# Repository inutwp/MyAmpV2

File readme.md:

Desktop Hybrid/Opamp Amp.

- 3CH Schema with DualOpamp Gain and DualOpamp / Discrete Buffer
- Discrete RailSpliter with Capacitance Multiplier

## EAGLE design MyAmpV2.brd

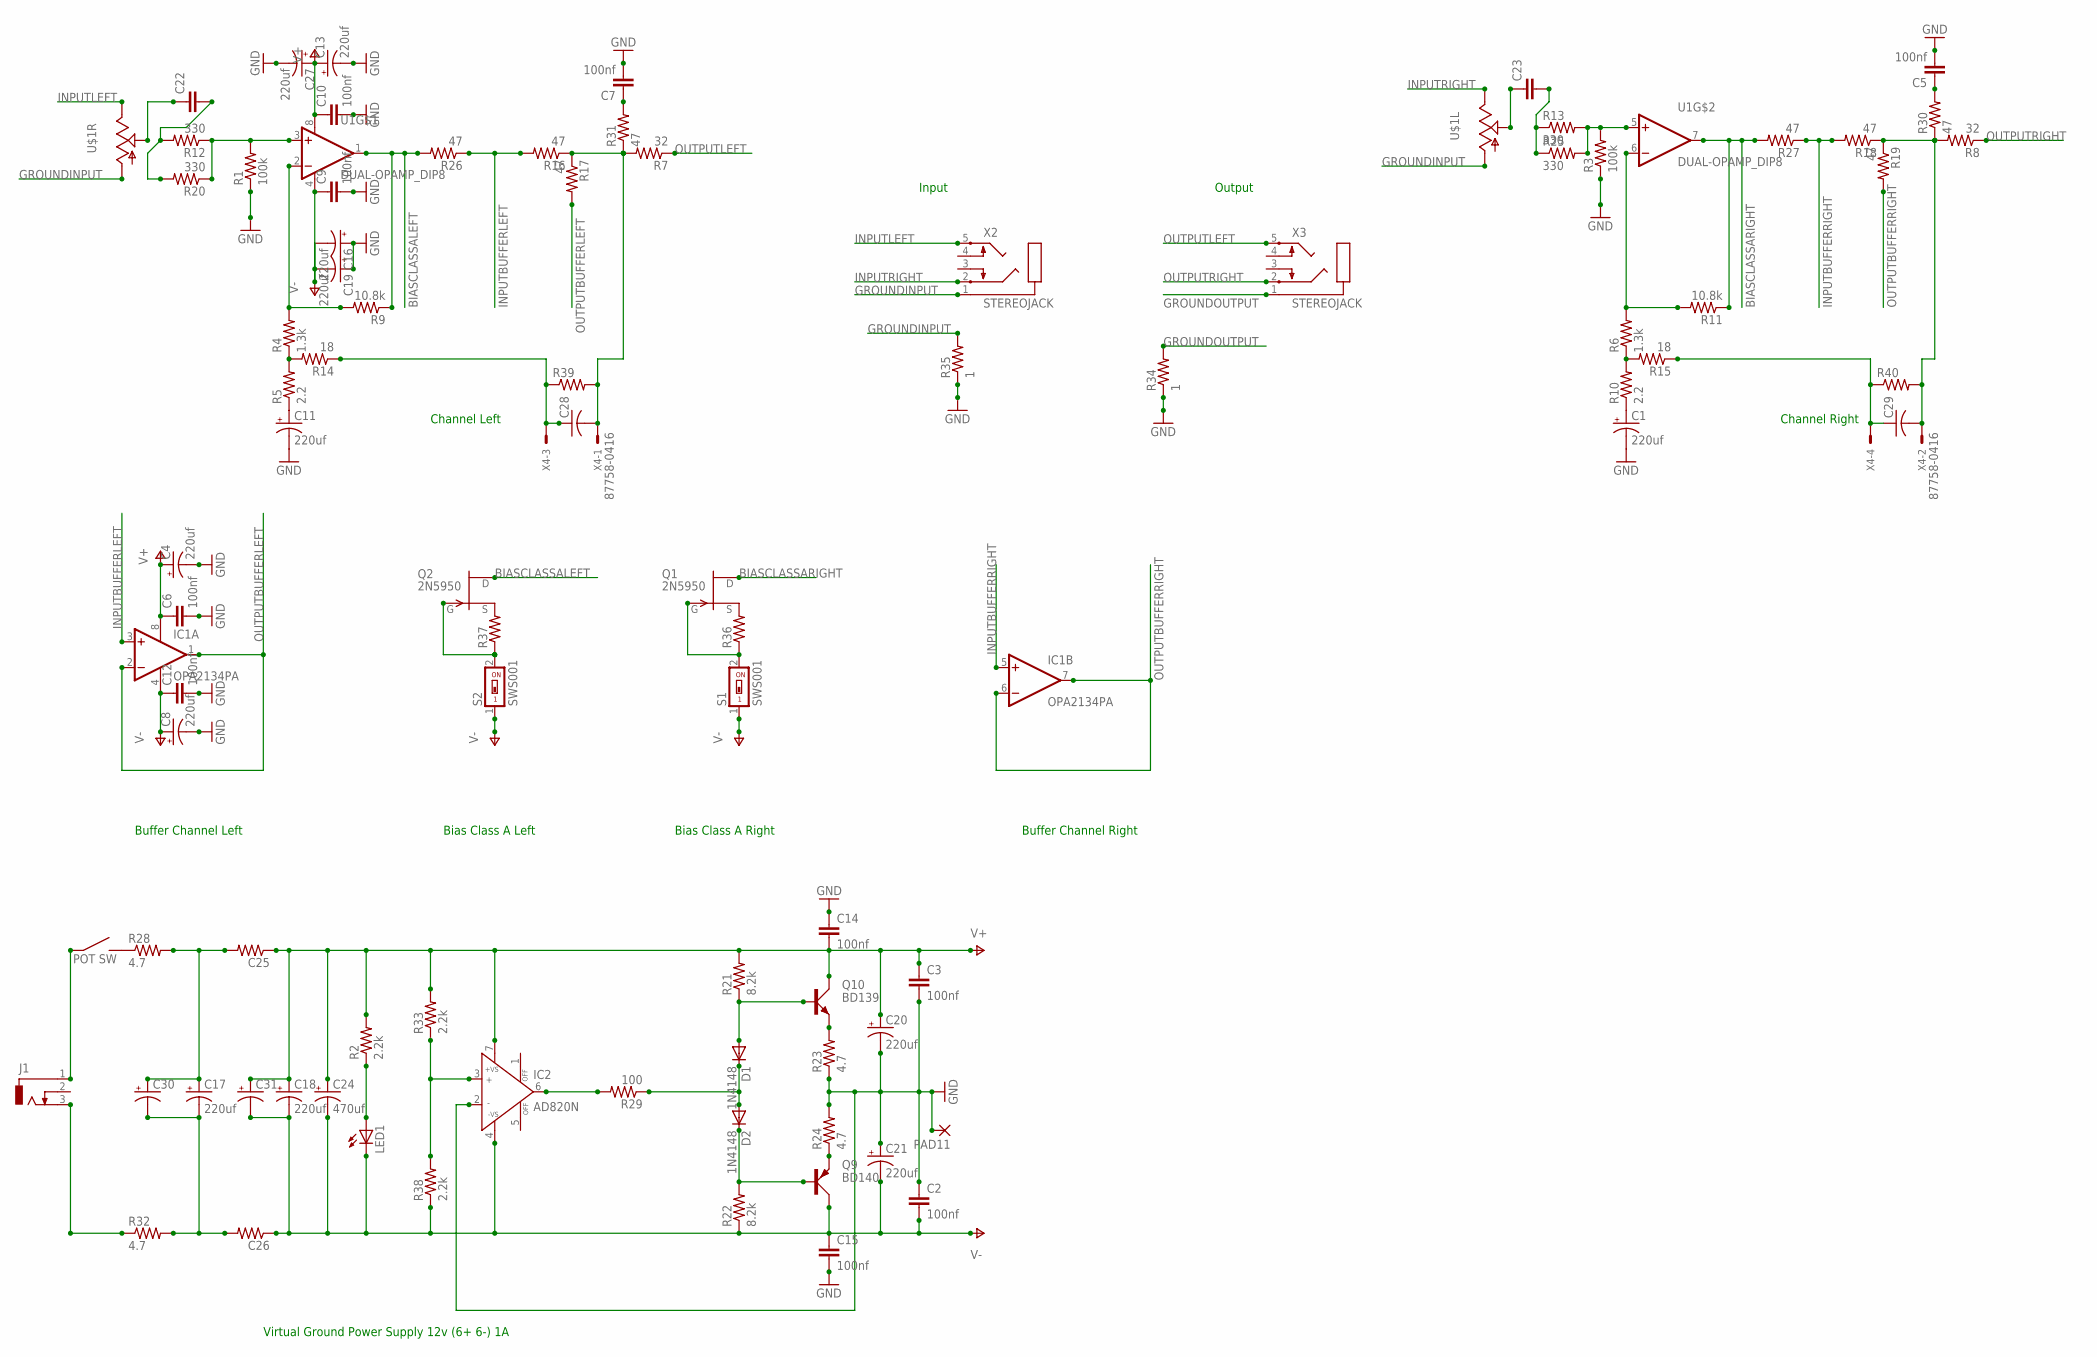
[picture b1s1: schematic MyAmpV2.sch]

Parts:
C1, C4, C8, C11, C13, C16, C17, C18, C19, C27: 220uf; E5-10,5
C2, C3, C5, C6, C7, C9, C10, C12, C14, C15: 100nf; C5B2.5
C20, C21: 220uf; D/7343-31R
C22, C23: C22/6; C22.5B6
C24: 470uf; E5-10,5
C25, C26: R-US_0207/12; 0207/12
C28, C29: C-USC1206K; C1206K
C30, C31: CPOL-USE7.5-16; E7,5-16
D1, D2: 1N4148; DO35-7
IC1: OPA2134PA; DIL08
IC2: AD820N; DIL08
J1: DCJ0303
LED1: LED3MM
PAD11: 1,6/0,9
Q1, Q2: 2N5950; TO-92
Q9: BD140; TO126AV
Q10: BD139; TO126AV
R1, R3: 100k; 0207/10
R2, R33, R38: 2.2k; 0207/10
R4, R6: 1.3k; 0207/10
R5, R10: 2.2; 0204/5
R7, R8: 32; 0207/12
R9, R11: 10.8k; 0207/10
R12, R13, R20, R25: 330; 0207/10
R14, R15: 18; 0207/12
R16, R17, R18, R19: 47; 0207/12
R21, R22: 8.2k; 0207/10
R23, R24, R28, R32: 4.7; 0207/10
R26, R27: 47; 0207/10
R29: 100; 0207/10
R30, R31: 47; 0207/7
R34, R35: 1; 0207/7
R36, R37: R-US_0204/5; 0204/5
R39, R40: R-US_MELF0204W; MINI_MELF-0204W
S1, S2: SWS001; SMS-001
U1: DUAL-OPAMP_DIP8; DIP-8
U$1: ALPS_RK0971221Z05; ALPS_RK0971221Z0X
X2, X3: STEREOJACK; STX3100
X4: 87758-0416

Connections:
BIASCLASSALEFT: Q2.3 (D), R9.1, R26.2, U1.1 (OUT)
BIASCLASSARIGHT: Q1.3 (D), R11.1, R27.2, U1.7 (OUT)
GND: C1.-, C2.1, C3.2, C4.-, C5.2, C6.2, C7.2, C8.-, C9.2, C10.2, C11.-, C12.2, C13.-, C14.1, C15.2, C16.+, C19.+, C20.-, C21.+, C27.-, IC2.2 (IN-), PAD11.1, R1.1, R3.1, R23.1, R24.2, R34.1, R35.1
GROUNDINPUT: R35.2, U$1.G1 (1), U$1.G2 (1), X2.1
GROUNDOUTPUT: R34.2, X3.1
INPUTBUFFERLEFT: IC1.3 (+IN), R16.2, R26.1
INPUTBUFFERRIGHT: IC1.5 (+IN), R18.2, R27.1
INPUTLEFT: U$1.I2 (3), X2.5
INPUTRIGHT: U$1.I1 (3), X2.2
unnamed: R1.2, R12.1, R20.1, U1.3 (+IN)
unnamed: C1.+, R10.1
unnamed: C22.2, R12.2, R20.2
unnamed: C11.+, R5.1
unnamed: IC2.6 (OUT), R29.2
unnamed: Q10.E, R23.2
unnamed: IC2.3 (IN+), R33.1, R38.2
unnamed: Q9.E, R24.1
unnamed: C22.1, U$1.O2 (2)
unnamed: R3.2, R13.2, R25.2, U1.5 (+IN)
unnamed: C23.2, R13.1, R25.1
unnamed: R4.1, R5.2, R14.2
unnamed: R4.2, R9.2, U1.2 (-IN)
unnamed: R6.1, R10.2, R15.2
unnamed: C23.1, U$1.O1 (2)
unnamed: C29.1, R15.1, R40.1, X4.4
unnamed: C28.2, R7.2, R16.1, R17.1, R31.1, R39.2, X4.1
unnamed: R6.2, R11.2, U1.6 (-IN)
unnamed: C28.1, R14.1, R39.1, X4.3
unnamed: R28.1, U$1.S2
unnamed: J1.3, R32.1
unnamed: C29.2, R8.2, R18.1, R19.1, R30.1, R40.2, X4.2
unnamed: LED1.A, R2.1
unnamed: J1.1, U$1.S1
unnamed: C5.1, R30.2
unnamed: D1.A, Q10.B, R21.1
unnamed: D2.C, Q9.B, R22.2
unnamed: C17.+, C25.2, C30.+, R28.2
unnamed: D1.C, D2.A, R29.1
unnamed: C7.1, R31.2
unnamed: C17.-, C26.2, C30.-, R32.2
unnamed: Q1.2 (S), R36.2
unnamed: Q2.1 (G), R37.1, S2.2
unnamed: Q1.1 (G), R36.1, S1.2
unnamed: Q2.2 (S), R37.2
OUTPUTBUFFERLEFT: IC1.1 (OUT), IC1.2 (-IN), R17.2
OUTPUTBUFFERRIGHT: IC1.6 (-IN), IC1.7 (OUT), R19.2
OUTPUTLEFT: R7.1, X3.5
OUTPUTRIGHT: R8.1, X3.2
V+: C3.1, C4.+, C6.1, C10.1, C13.+, C14.2, C18.+, C20.+, C24.+, C25.1, C27.+, C31.+, IC1.8 (V+), IC2.7 (+VS), Q10.C, R2.2, R21.2, R33.2, U1.8 (V+)
V-: C2.2, C8.+, C9.1, C12.1, C15.1, C16.-, C18.-, C19.-, C21.-, C24.-, C26.1, C31.-, IC1.4 (V-), IC2.4 (-VS), LED1.K (C), Q9.C, R22.1, R38.1, S1.1, S2.1, U1.4 (V-)

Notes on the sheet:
Virtual Ground Power Supply 12v (6+ 6-) 1A
Channel Left
Buffer Channel Left
Bias Class A Left
Channel Right
Bias Class A Right
Buffer Channel Right
Input
Output

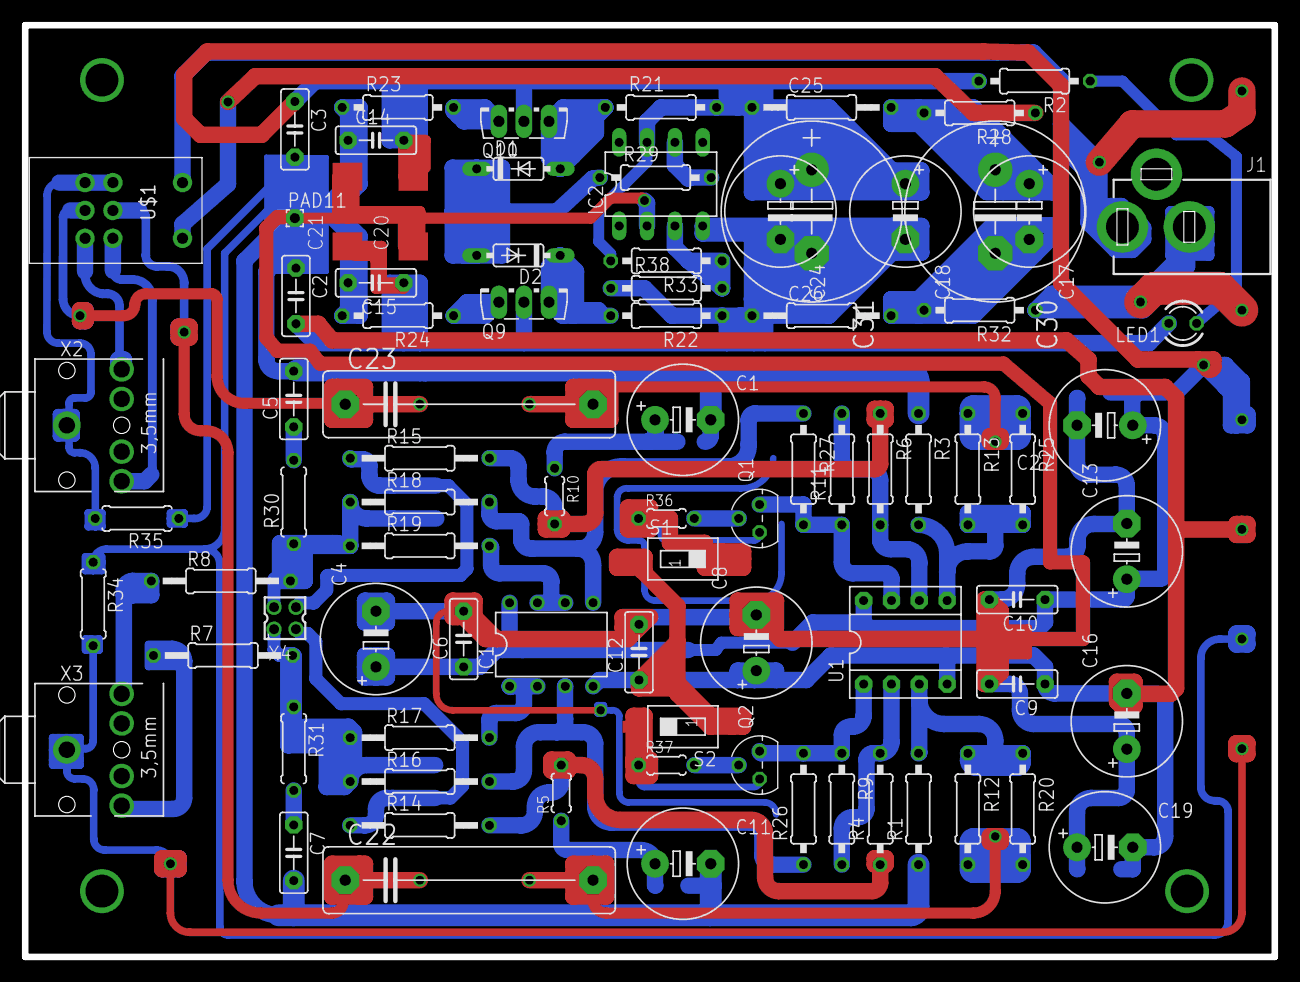
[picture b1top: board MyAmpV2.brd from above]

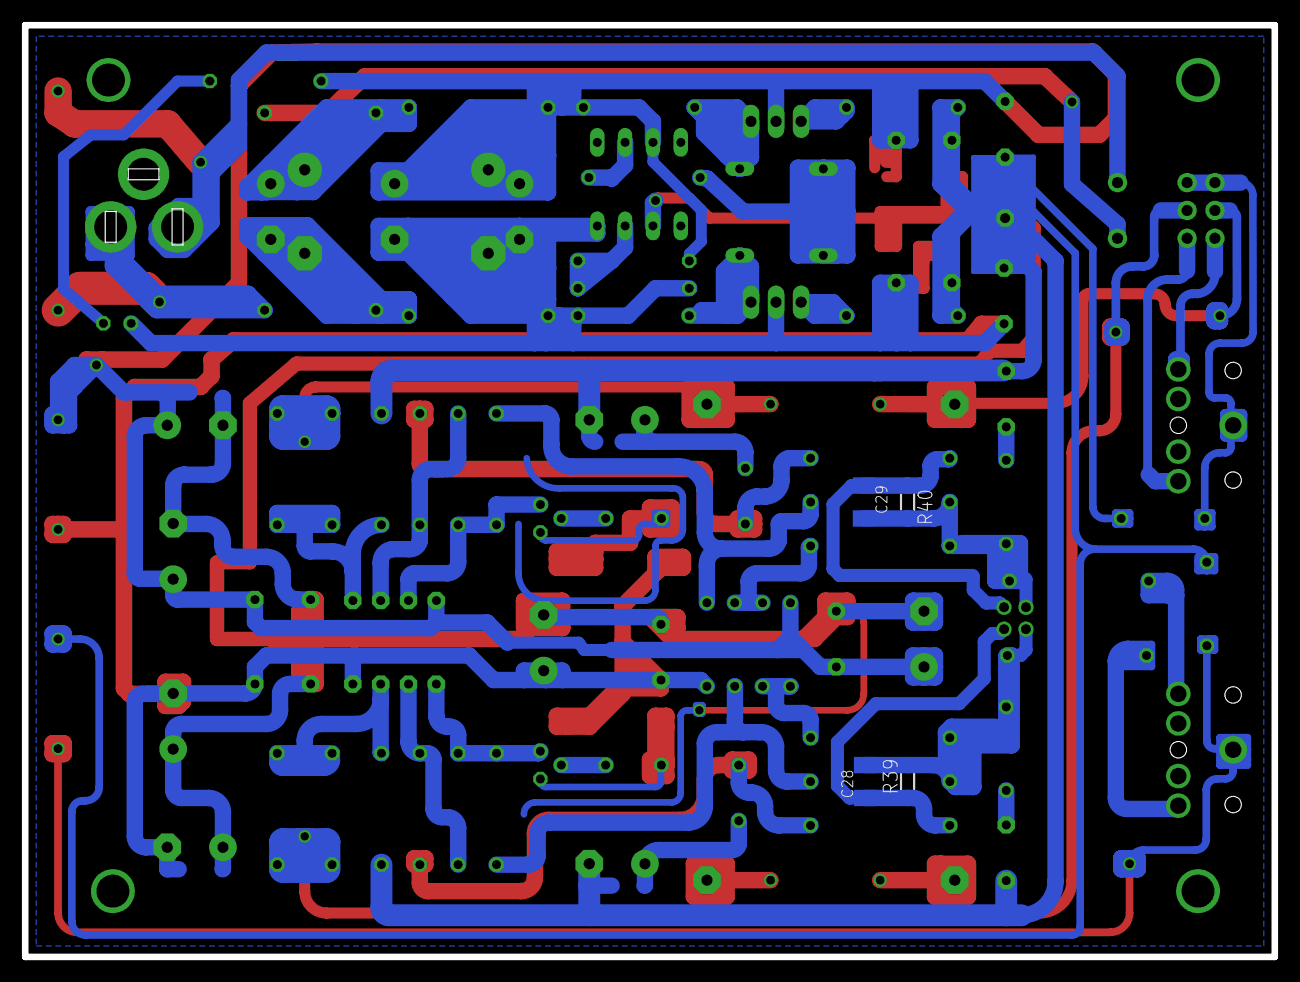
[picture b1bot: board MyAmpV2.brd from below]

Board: 2 copper layers, 114.0 x 85.0 mm, 89 parts (4 on the bottom side), 50 nets.

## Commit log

2021-11-05 add image on readme
